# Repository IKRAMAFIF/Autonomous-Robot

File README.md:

# 🤖 Projet CATRONIC : Robot Autonome "Chat et Souris"

> **Auteurs :** AFIF Ikram, AIT ALLA Hajar, MENJLI Fakhri

> **Encadré par :** Laurent FIACK, Nicolas PAPAZOGLOU

> **Année académique :** 2025/2026

Le robot **CATRONIC** est un système embarqué autonome conçu pour simuler un jeu de chat et de souris entre plusieurs robots identiques. Les robots évoluent sur une table sans bordures et sont capables de détecter les bords pour éviter toute chute.

---

##  Table des matières
- [Stratégie de fonctionnement](#stratégie-de-fonctionnement)
- [Architecture du système](#architecture-du-système-global)
  - [Schémas généraux](#schémas-généraux)
  - [Sous-systèmes](#sous-systèmes)
- [Nomenclature (Bill of Materials)](#nomenclature-bill-of-materials)
- [Structure logicielle et FreeRTOS](#structure-logicielle-et-freertos)
- [Tests et validation](#tests-et-validation)
- [Test final](#test-final)
- [Conclusion](#conclusion)

---

##  Stratégie de fonctionnement

La logique du robot est orchestrée par un noyau temps réel (**FreeRTOS**), permettant de gérer plusieurs tâches simultanément pour une réactivité maximale.

### Détection de l'environnement

- **Détection des bords :** Le robot utilise des **capteurs mécaniques Würth WS-MITV** positionnés à l’avant, à l’arrière, à gauche et à droite. Lorsqu’un capteur détecte le vide, il déclenche une interruption qui ordonne un changement immédiat de direction pour éviter la chute.  
- **Détection des adversaires :** Le **LIDAR YDLIDAR X2** scanne l’environnement à 360° et transmet en temps réel la position et la distance des autres robots.  
- **Détection des collisions :** L’**accéléromètre ADXL343** détecte les chocs par variation brutale d’accélération. Il est également utilisé comme arrêt d’urgence manuel.

### Modes de jeu

- **Mode Souris 🐭 :** Le robot cherche à maximiser la distance avec le “chat” tout en évitant les bords de la table.  
- **Mode Chat 🐱 :** Le robot identifie la “souris” la plus proche via le LIDAR et cherche à la percuter.

---

##  Architecture du système global

L’architecture est organisée autour de cinq sous-ensembles principaux : **alimentation**, **commande**, **acquisition**, **déplacement** et **interface utilisateur**.

### Schémas généraux

Vues d’ensemble de l’architecture matérielle :

**Figure 1 – Diagramme d’architecture fonctionnelle du robot:**

**Figure 2 – Schéma global du système:**

**Figure 3 – Routage du PCB principal:**

**Figure 4 – Vue 3D du PCB sous KiCad:**

### Sous-systèmes

####  Alimentation
Le robot est alimenté par une batterie **NiMH 7.2V**, régulée en **5V** pour le LIDAR et en **3.3V** pour le reste des composants.

*Figure 5 – Schéma d’alimentation du robot.*

####  Commande
Le cœur du système repose sur un **STM32G431CBU6** (ARM Cortex-M4) exécutant **FreeRTOS** pour coordonner les différentes tâches.

*Figure 6 – Schéma de la carte de commande STM32.*

#### Acquisition
Ce sous-système regroupe les capteurs assurant la perception de l’environnement.

*Figure 7 – Sous-système de détection (LIDAR, accéléromètre, capteurs WS-MITV).* 

####  Déplacement
Deux moteurs DC, commandés par des **drivers ZXBM5210-SP-13**, permettent un contrôle précis de la vitesse et de la direction via des signaux PWM.

*Figure 8 – Schéma des moteurs et drivers.*

####  Interface utilisateur
Interrupteur, bouton de démarrage, LED de statut et connecteur SWD pour le débogage.

---

##  Nomenclature (Bill of Materials)

| Composant | Référence | Datasheet |
|:---|:---|:---|
| Microcontrôleur | STM32G431CBU6 | [Datasheet](https://www.st.com/resource/en/datasheet/stm32g431c6.pdf) |
| Driver moteur | ZXBM5210-SP-13 | [Datasheet](https://www.mouser.fr/datasheet/3/175/1/ZXBM5210.pdf) |
| Accéléromètre | ADXL343BCCZ-RL | [Datasheet](https://www.analog.com/media/en/technical-documentation/data-sheets/adxl343.pdf) |
| LIDAR | YDLIDAR X2 | [Datasheet](https://cdn.robotshop.com/media/y/ydl/rb-ydl-04/pdf/ydlidar-x2-360-laser-scanner-datasheet2.pdf) |
| Régulateur 5V | MP1475DJ-LF-P | [Datasheet](https://www.farnell.com/datasheets/2915024.pdf) |
| Régulateur 3.3V | BU33SD5WG-TR | [Datasheet](https://fscdn.rohm.com/en/products/databook/datasheet/ic/power/linear_regulator/buxxsd5wg-e.pdf) |
| Batterie | NiMH 7.2V 1.3Ah | [Datasheet](https://fr.rs-online.com/web/p/blocs-batteries-rechargeables/7770377) |
| Capteur bordure | WS-MITV THT | [Datasheet](https://www.we-online.com/en/components/products/MITV_12_8X5_8_THT__LEVER_LEFT_55GF) |
| Bluetooth | HC-05 | [Datasheet](https://components101.com/sites/default/files/component_datasheet/HC-05%20Datasheet.pdf) |
| Boutons poussoirs | Wurth 430182070816 | [Datasheet](https://www.we-online.com/components/products/datasheet/430182070816.pdf) |
| Interrupteur ON/OFF | Wurth 472121020311 | [Datasheet](https://www.we-online.com/components/products/datasheet/472121020311.pdf) |

---
## Fichiers sources principaux

-   **`main.c`** : Point d'entrée du programme. Ce fichier initialise le microcontrôleur, tous les périphériques (GPIO, I2C, UART, Timers), les pilotes (moteurs, LIDAR), et crée les quatre tâches FreeRTOS qui orchestrent le comportement du robot.
-   **`robot_logic.c`** : Cœur de l'intelligence du robot. Il contient l'implémentation des tâches FreeRTOS qui gèrent la logique de jeu, la détection des collisions et des bordures, ainsi que la communication.
-   **`MoteurPWM.c`** : Pilote pour le contrôle des moteurs DC. Il fournit des fonctions pour initialiser les moteurs, et contrôler leur vitesse via des signaux PWM.
-   **`ADXL343_driver.c`** : Pilote pour l'accéléromètre ADXL343. Il gère l'initialisation du capteur et la détection de chocs.
-   **`driver_LIDAR.c`** : Pilote pour le capteur LIDAR YDLIDAR X2. Il traite les données brutes reçues via UART DMA pour en extraire la distance et l'angle des obstacles.
-   **`border_sensors.c`** : Gère la logique des capteurs de bordure.
-   **`drv_bt.c`** : Assure la gestion de la communication Bluetooth (HC-05), notamment la réception de commandes.

##  Structure logicielle et FreeRTOS

Le comportement du robot est géré par **quatre tâches FreeRTOS** principales :

1.  **`BorderTask`**
    -   **Rôle :** Surveille en permanence les capteurs de bordure.
    -   **Fonctionnement :** À intervalle régulier (100 ms), la tâche lit l'état des capteurs. Si un bord est détecté, elle met à jour une variable globale (`border_active`) protégée par un mutex pour signaler l'état et la direction du bord détecté à la tâche principale `RobotModeTask`.

2.  **`ShockTask`**
    -   **Rôle :** Détecte les collisions et inverse les rôles "Chat" et "Souris".
    -   **Fonctionnement :** La tâche initialise l'accéléromètre pour la détection de chocs. Elle vérifie en continu si un choc a eu lieu. Si c'est le cas, elle change l'état du robot (`robot_mode`) de `CHAT` à `SOURIS` ou inversement.

3.  **`BluetoothTask`**
    -   **Rôle :** Traite les commandes reçues via Bluetooth.
    -   **Fonctionnement :** La tâche attend de recevoir des commandes utilisateur. Elle peut ainsi forcer le robot à s'arrêter (`STOP`), à démarrer (`START`), ou à passer en mode `CHAT` ou `SOURIS`, offrant un contrôle manuel sur le comportement du robot.

4.  **`RobotModeTask`**
    -   **Rôle :** Tâche principale qui exécute la logique de déplacement et de jeu.
    -   **Fonctionnement :** C'est la tâche la plus complexe. À chaque cycle :
        -   Elle vérifie l'état de la variable `border_active`. Si un bord est détecté, elle exécute une manœuvre d'évitement prioritaire (reculer puis tourner) pour empêcher le robot de tomber.
        -   Si aucun bord n'est détecté, elle exécute la logique de jeu en fonction de la variable `robot_mode` :
            -   **Mode `ROBOT_STOP` :** Les moteurs sont à l'arrêt.
            -   **Mode `ROBOT_MODE_CHAT` (Poursuite) :** La tâche analyse les données du LIDAR pour trouver l'obstacle le plus proche. Si l'obstacle est en face, elle commande au robot d'avancer. Sinon, elle le fait tourner pour se diriger vers la cible.
            -   **Mode `ROBOT_MODE_SOURIS` (Fuite) :** Si un obstacle (le "chat") est détecté à moins de 30 cm, le robot recule pour s'en éloigner. Sinon, il continue d'avancer pour explorer la zone de jeu.
        -   Si aucun obstacle n'est détecté par le LIDAR, le robot s'arrête.

---

##  Tests et validation

Pour garantir la fiabilité du système, plusieurs séries de tests ont été menées.

### Test de déplacement et moteurs

Ce test valide le contrôle PWM et met en évidence les écarts de vitesse entre les moteurs. 
Un ajustement asymétrique des vitesses a permis d’améliorer la précision du déplacement du robot.

### Test de détection de bordures/détection de collision

Ce test est crucial pour la sécurité du robot. Il valide la robustesse des capteurs mécaniques, et la détection des chocs via l'accéléromètre qui déclenche le changement de rôle du robot
- **Approche frontale :** Le robot est dirigé droit vers le bord de la table. On vérifie qu'il s'arrête et recule à chaque fois, sans chute.
- **Approche en diagonale :** Le test est répété avec différents angles d'approche pour s'assurer que le levier du capteur est bien actionné même lorsque le robot n'est pas perpendiculaire au bord.
- **Fiabilité :** Répétition du test des dizaines de fois pour garantir la reproductibilité et la fiabilité du mécanisme.
- **Changement de mode après impact :** Après une collision détectée par l'accéléromètre, on vérifie que les rôles "Chat" et "Souris" sont bien inversés.

*Figure 9 – Détection de bordures/chocs et changement de direction.*

### Test du LIDAR et logique de jeu

Ce test valide la perception de l'environnement et la stratégie comportementale.
- **Fiabilité de la détection d'adversaire :** Vérification que le LIDAR détecte de manière fiable la position de l'autre robot.
- **Logique de poursuite/fuite :** Validation de la trajectoire du robot en fonction des données du LIDAR (le "Chat" se rapproche de la "Souris", et la "Souris" s'en éloigne).

*Figure 10 – Données LIDAR capturées via Tera Term (UART DMA).* 

### Test Bluetooth

Ce test vérifie la connectivité et la fiabilité de la communication sans fil via le module Bluetooth HC-05.

- **Connexion :** Vérification de l'établissement de la connexion Bluetooth avec un appareil externe.

- **Transmission de données :** Test de l'envoi et de la réception de données entre le robot et l'appareil connecté.

- **Changement de mode à distance :** Validation de la capacité à modifier le rôle du robot (Chat/Souris) via une commande Bluetooth.

*Figure 11 – Communication Bluetooth et affichage des données.*

---
## Structure du dépôt GitHub

```
├── Firmware/           → Code STM32CubeIDE 
├── Hardware/           → Schémas, PCB et vues 3D KiCad
├── Media/              → Illustrations et résultats de tests
└── README.md           → Présentation du projet
```

---
##  Test final

Lors du test final, le robot a validé plusieurs fonctionnalités clés. Les capteurs de bordure fonctionnent correctement, permettant au robot de détecter les limites de la surface et d’éviter toute chute. La commande via Bluetooth est également opérationnelle : il est possible de sélectionner le mode de fonctionnement du robot ainsi que d’envoyer des commandes Start et Stop pour lancer ou arrêter le système. Les données du LiDAR ont pu être lues avec succès, cependant toutes les mesures n’étaient pas fiables et l’intégration complète du capteur dans le système embarqué n’a pas pu être finalisée. En conséquence, le robot n’est pas capable de détecter les autres robots à ce stade. Enfin, l’accéléromètre permet de détecter les chocs lors d’une collision, déclenchant automatiquement un changement de mode de fonctionnement du robot.

---
## Conclusion

Ce projet a permis de concevoir et de mettre en œuvre un robot mobile intégrant plusieurs capteurs et modes de fonctionnement. Les tests finaux ont validé avec succès la détection des bordures, la commande via Bluetooth avec sélection des modes ainsi que la gestion des collisions à l’aide de l’accéléromètre. Ces fonctionnalités assurent un fonctionnement sûr et contrôlable du robot.

Cependant, certains défis techniques ont été rencontrés, notamment lors de l’exploitation et de l’intégration du LiDAR. Bien que les données aient pu être lues, leur fiabilité et leur intégration complète dans l’architecture embarquée n’ont pas pu être finalisées, empêchant la détection des autres robots. Ces limitations sont principalement liées aux contraintes de temps et à la complexité du traitement des données capteur.

Ce travail a néanmoins permis d’acquérir une expérience pratique solide en systèmes embarqués, en communication sans fil et en intégration capteurs. Des perspectives d’amélioration incluent l’optimisation du traitement des données LiDAR, l’amélioration de la fusion capteurs et l’extension des capacités de détection du robot.

---

<p align="center">
  2026 — Projet académique ENSEA
  <br>Développement d’un robot autonome Chat–Souris 
</p>

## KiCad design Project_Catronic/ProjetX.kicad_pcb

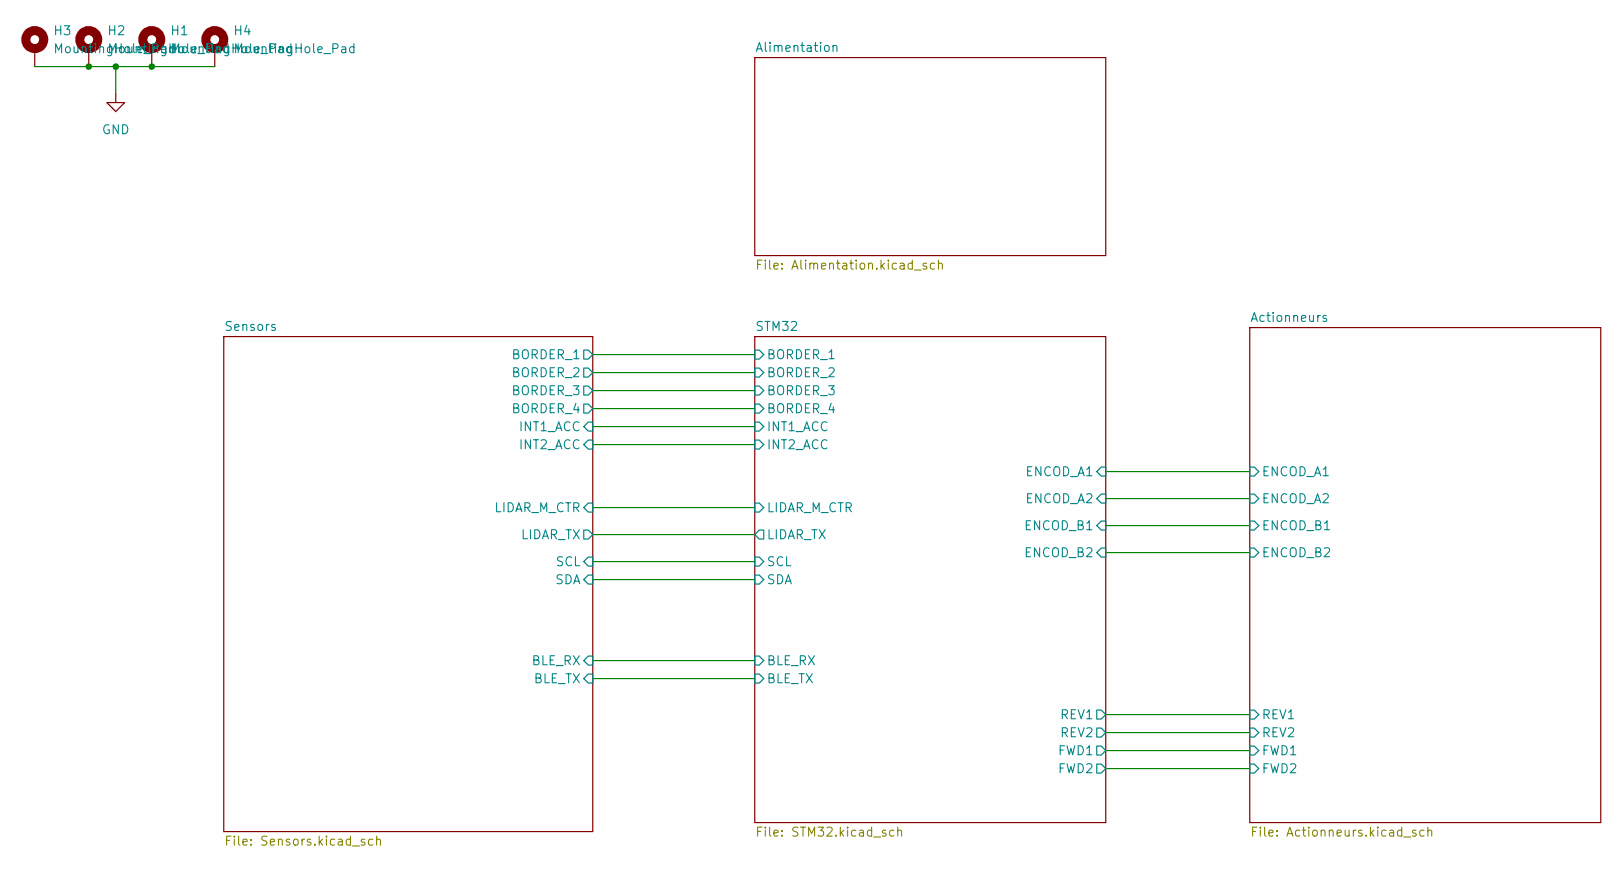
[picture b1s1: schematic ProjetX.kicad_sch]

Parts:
H1, H2, H3, H4: MountingHole_Pad; MountingHole_3.2mm_M3_Pad_Via

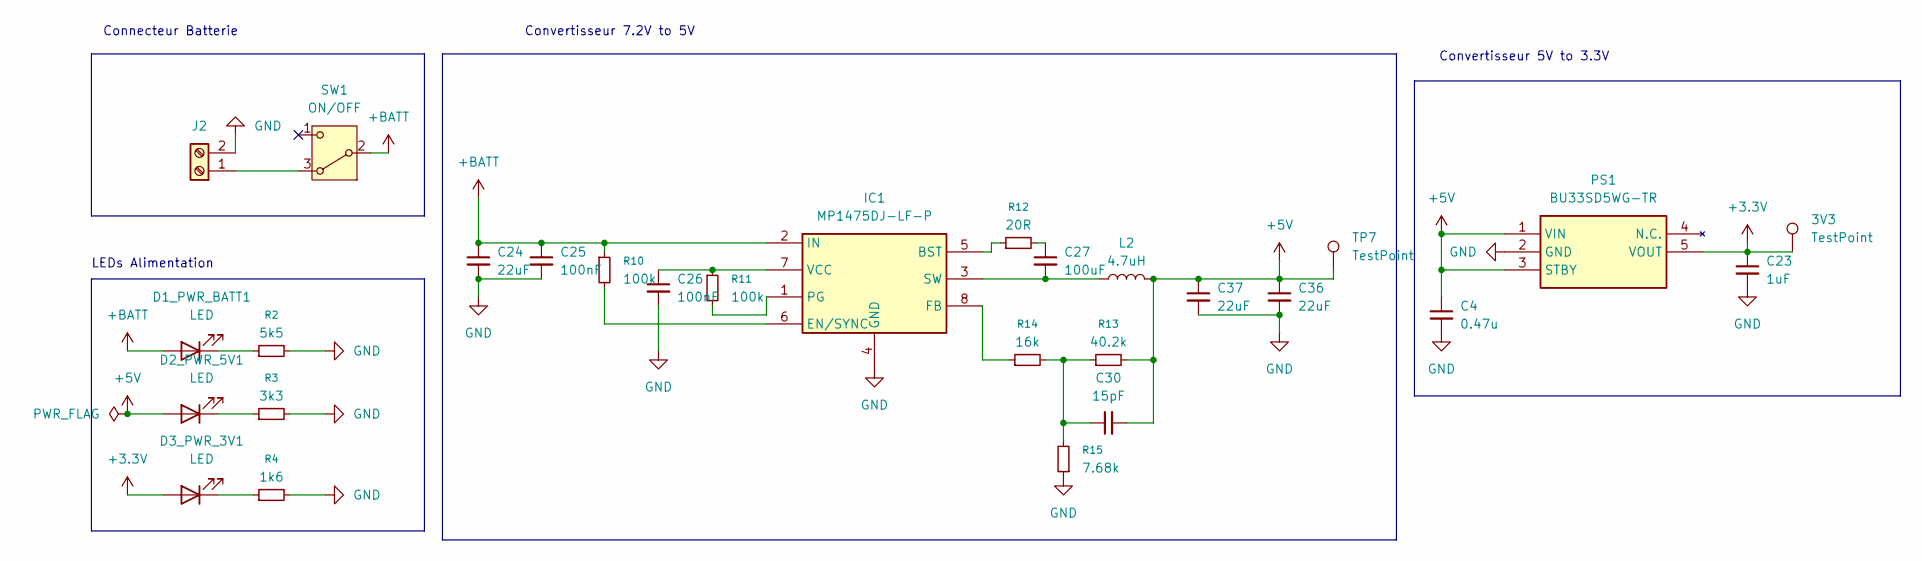
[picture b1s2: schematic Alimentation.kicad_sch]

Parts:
3V3: TestPoint; TestPoint_Pad_D1.0mm
C4: 0.47u; C_0402_1005Metric
C23: 1uF; C_0402_1005Metric
C24, C36, C37: 22uF; C_0805_2012Metric
C25, C26: 100nF; C_0402_1005Metric
C27: 100uF; C_0402_1005Metric
C30: 15pF; C_0402_1005Metric
D1_PWR_BATT1: LED; LED_0603_1608Metric; MPN 150060GS55040
D2_PWR_5V1: LED; LED_0603_1608Metric; MPN 150060BS55040
D3_PWR_3V1: LED; LED_0603_1608Metric; MPN 150060RS55040
IC1: MP1475DJ-LF-P; TSOT-23-8; Manufacturer_Part_Number MP1475DJ-LF-P
J2: Screw_Terminal_01x02; JST_XH_S2B-XH-A_1x02_P2.50mm_Horizontal
L2: 4.7uH; L_Wuerth_HCI-5040
PS1: BU33SD5WG-TR; TSOT-23-5; Manufacturer_Part_Number BU33SD5WG-TR
R2: 5k5; R_0402_1005Metric
R3: 3k3; R_0402_1005Metric
R4: 1k6; R_0402_1005Metric
R10, R11: 100k; R_0402_1005Metric
R12: 20R; R_0402_1005Metric
R13: 40.2k; R_0402_1005Metric
R14: 16k; R_0402_1005Metric
R15: 7.68k; R_0402_1005Metric
SW1: ON/OFF; Nidec_Copal_CAS-120A; MPN 777-0377
TP7: TestPoint; TestPoint_Pad_D1.0mm

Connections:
+3.3V: 3V3.1, C23.1, D3_PWR_3V1.2 (A), PS1.5 (VOUT); also elsewhere on the board
+5V: C4.1, C30.2, C36.1, C37.1, D2_PWR_5V1.2 (A), L2.2, PS1.1 (VIN), PS1.3 (STBY), R13.2, TP7.1; also elsewhere on the board
+BATT: C24.1, C25.1, D1_PWR_BATT1.2 (A), IC1.2 (IN), R10.1, SW1.2 (B); also elsewhere on the board
unnamed: C27.1, R12.2
unnamed: C30.1, R13.1, R14.2, R15.2
unnamed: D1_PWR_BATT1.1 (K), R2.1
unnamed: D2_PWR_5V1.1 (K), R3.1
unnamed: D3_PWR_3V1.1 (K), R4.1
unnamed: IC1.5 (BST), R12.1
unnamed: IC1.6 (EN/SYNC), R10.2
unnamed: IC1.8 (FB), R14.1
unnamed: IC1.1 (PG), R11.2
unnamed: C27.2, IC1.3 (SW), L2.1
unnamed: C26.1, IC1.7 (VCC), R11.1

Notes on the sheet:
Convertisseur 7.2V to 5V
Connecteur Batterie
Convertisseur 5V to 3.3V
LEDs Alimentation

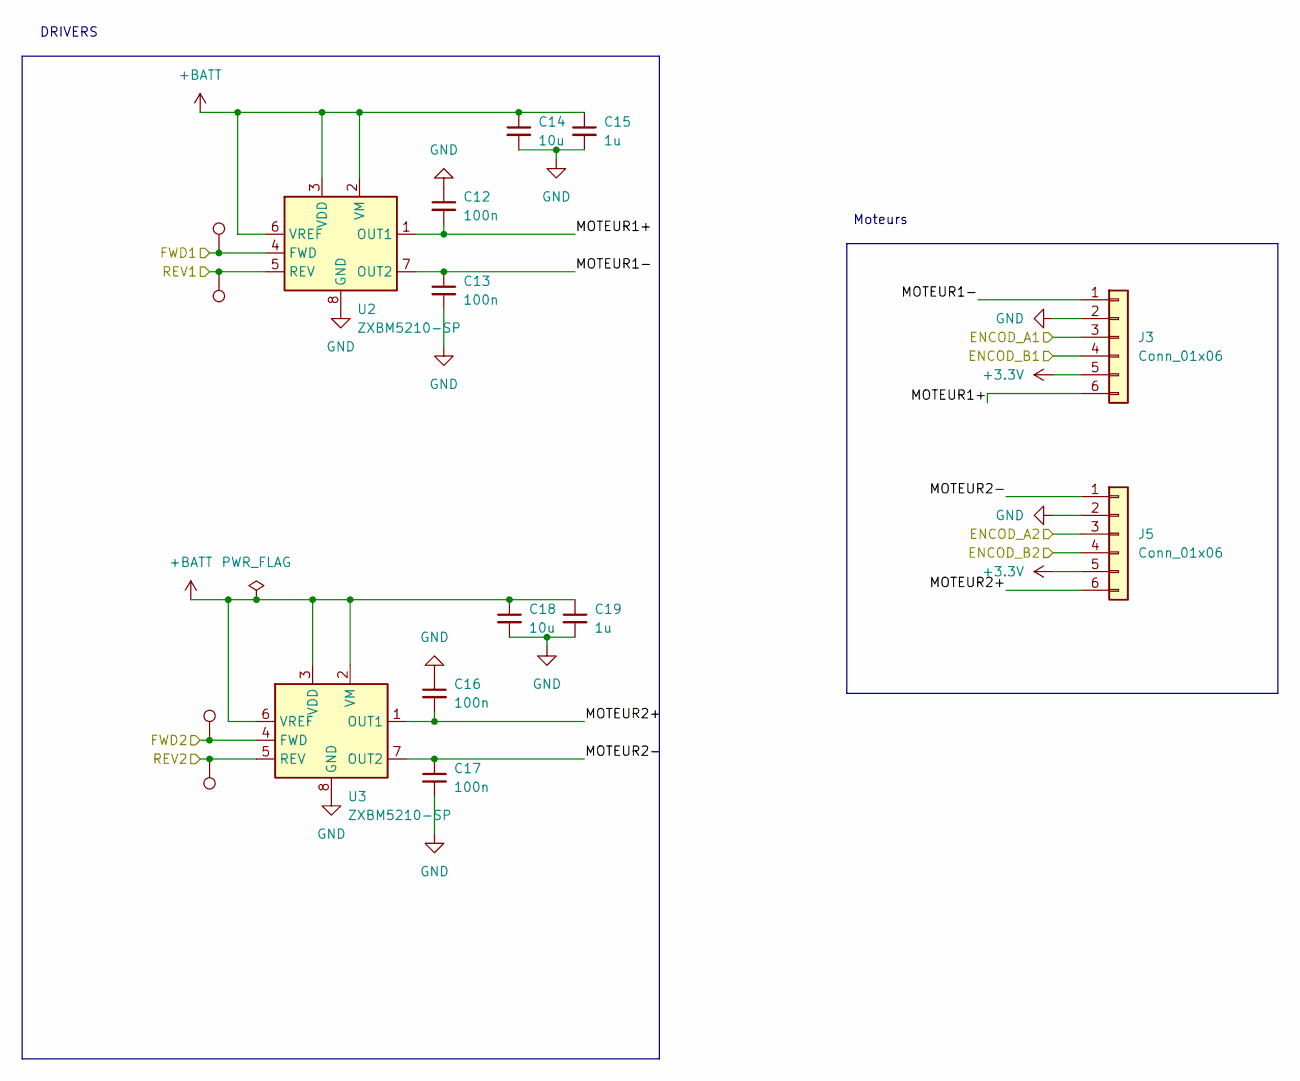
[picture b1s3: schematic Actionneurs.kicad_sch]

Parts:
C12, C13, C16, C17: 100n; C_0402_1005Metric
C14, C18: 10u; C_0402_1005Metric
C15, C19: 1u; C_0402_1005Metric
J3, J5: Conn_01x06; JST_XH_S6B-XH-A_1x06_P2.50mm_Horizontal; MPN DfRobot FIT0521
TP1, TP2, TP3, TP4: TestPoint; TestPoint_Pad_D1.0mm
U2, U3: ZXBM5210-SP; Diodes_SO-8EP; MPN ZXBM5210-SP

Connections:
+3.3V: J3.5, J5.5; also elsewhere on the board
+BATT: C14.1, C15.1, C18.1, C19.1, U2.2 (VM), U2.3 (VDD), U2.6 (VREF), U3.2 (VM), U3.3 (VDD), U3.6 (VREF); also elsewhere on the board
/Actionneurs/ENCOD_A1: J3.3; also elsewhere on the board
/Actionneurs/ENCOD_A2: J5.3; also elsewhere on the board
/Actionneurs/ENCOD_B1: J3.4; also elsewhere on the board
/Actionneurs/ENCOD_B2: J5.4; also elsewhere on the board
/Actionneurs/FWD1: TP1.1, U2.4 (FWD); also elsewhere on the board
/Actionneurs/FWD2: TP3.1, U3.4 (FWD); also elsewhere on the board
/Actionneurs/MOTEUR1+: C12.2, J3.6, U2.1 (OUT1)
/Actionneurs/MOTEUR1-: C13.1, J3.1, U2.7 (OUT2)
/Actionneurs/MOTEUR2+: C16.2, J5.6, U3.1 (OUT1)
/Actionneurs/MOTEUR2-: C17.1, J5.1, U3.7 (OUT2)
/Actionneurs/REV1: TP2.1, U2.5 (REV); also elsewhere on the board
/Actionneurs/REV2: TP4.1, U3.5 (REV); also elsewhere on the board

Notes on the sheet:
DRIVERS
Moteurs

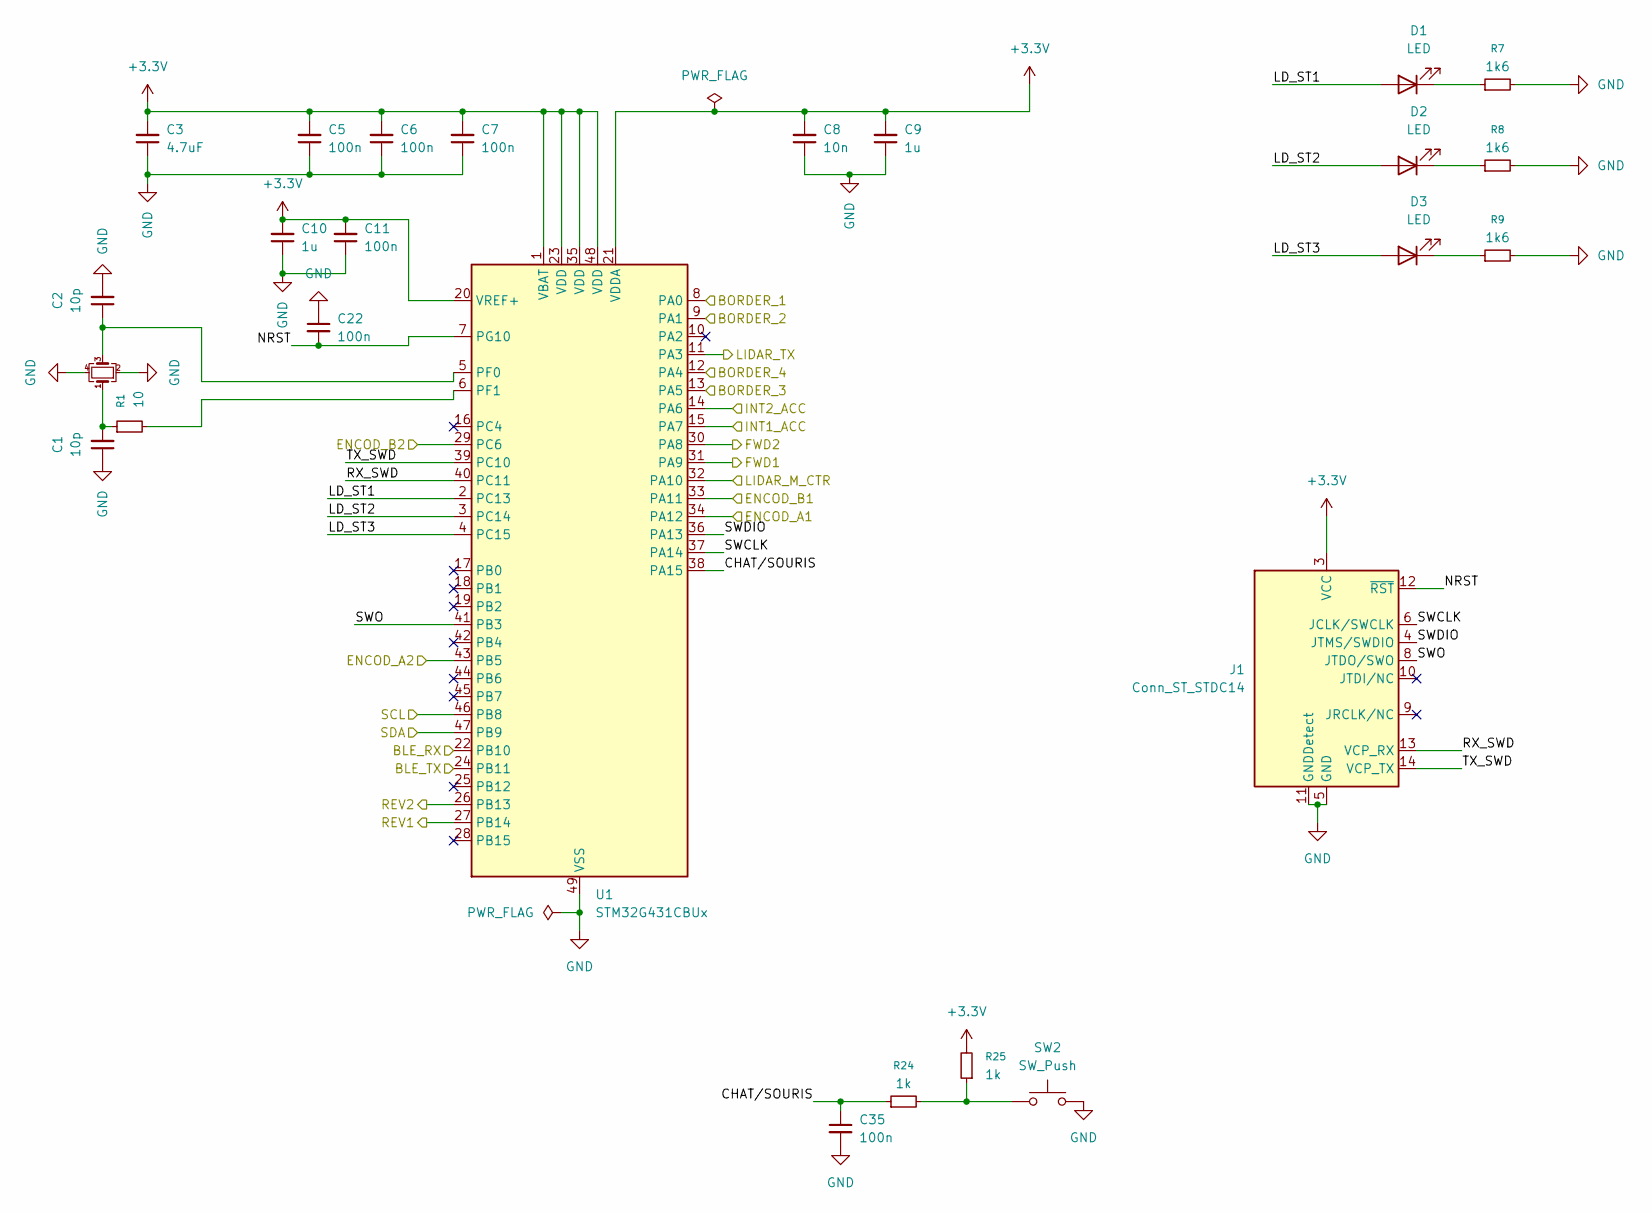
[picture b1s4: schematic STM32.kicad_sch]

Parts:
C1, C2: 10p; C_0402_1005Metric
C3: 4.7uF; C_0603_1608Metric
C5, C6, C7, C11, C22, C35: 100n; C_0402_1005Metric
C8: 10n; C_0402_1005Metric
C9, C10: 1u; C_0402_1005Metric
D1, D2, D3: LED; LED_0603_1608Metric; MPN 150060RS55040
J1: Conn_ST_STDC14; PinHeader_2x07_P1.27mm_Vertical_SMD; MPN SAMTEC FTSH-107-01-L-DV-K-A.
R1: 10; R_0402_1005Metric
R7, R8, R9: 1k6; R_0402_1005Metric
R24, R25: 1k; R_0402_1005Metric
SW2: SW_Push; SW_PUSH_6mm_H9.5mm
U1: STM32G431CBUx; QFN-48-1EP_7x7mm_P0.5mm_EP5.6x5.6mm; MPN STM32G4316B
Y1: Crystal_GND24_Small; Crystal_SMD_EuroQuartz_MT-4Pin_3.2x2.5mm

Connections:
+3.3V: C3.2, C5.2, C6.2, C7.2, C8.2, C9.2, C10.2, C11.2, J1.3 (VCC), R25.2, U1.1 (VBAT), U1.20 (VREF+), U1.21 (VDDA), U1.23 (VDD), U1.35 (VDD), U1.48 (VDD); also elsewhere on the board
/Actionneurs/ENCOD_A1: U1.34 (PA12); also elsewhere on the board
/Actionneurs/ENCOD_A2: U1.43 (PB5); also elsewhere on the board
/Actionneurs/ENCOD_B1: U1.33 (PA11); also elsewhere on the board
/Actionneurs/ENCOD_B2: U1.29 (PC6); also elsewhere on the board
/Actionneurs/FWD1: U1.31 (PA9); also elsewhere on the board
/Actionneurs/FWD2: U1.30 (PA8); also elsewhere on the board
/Actionneurs/REV1: U1.27 (PB14); also elsewhere on the board
/Actionneurs/REV2: U1.26 (PB13); also elsewhere on the board
/STM32/BLE_RX: U1.22 (PB10); also elsewhere on the board
/STM32/BLE_TX: U1.24 (PB11); also elsewhere on the board
/STM32/BORDER_1: U1.8 (PA0); also elsewhere on the board
/STM32/BORDER_2: U1.9 (PA1); also elsewhere on the board
/STM32/BORDER_3: U1.13 (PA5); also elsewhere on the board
/STM32/BORDER_4: U1.12 (PA4); also elsewhere on the board
/STM32/CHAT/SOURIS: C35.1, R24.1, U1.38 (PA15)
/STM32/INT1_ACC: U1.15 (PA7); also elsewhere on the board
/STM32/INT2_ACC: U1.14 (PA6); also elsewhere on the board
/STM32/LD_ST1: D1.2 (A), U1.2 (PC13)
/STM32/LD_ST2: D2.2 (A), U1.3 (PC14)
/STM32/LD_ST3: D3.2 (A), U1.4 (PC15)
/STM32/LIDAR_M_CTR: U1.32 (PA10); also elsewhere on the board
/STM32/LIDAR_TX: U1.11 (PA3); also elsewhere on the board
/STM32/NRST: C22.2, J1.12 (~RST), U1.7 (PG10)
/STM32/RX_SWD: J1.13 (VCP_RX), U1.40 (PC11)
/STM32/SCL: U1.46 (PB8); also elsewhere on the board
/STM32/SDA: U1.47 (PB9); also elsewhere on the board
/STM32/SWCLK: J1.6 (JCLK/SWCLK), U1.37 (PA14)
/STM32/SWDIO: J1.4 (JTMS/SWDIO), U1.36 (PA13)
/STM32/SWO: J1.8 (JTDO/SWO), U1.41 (PB3)
/STM32/TX_SWD: J1.14 (VCP_TX), U1.39 (PC10)
unnamed: C1.2, R1.1, Y1.1
unnamed: D1.1 (K), R7.1
unnamed: D2.1 (K), R8.1
unnamed: D3.1 (K), R9.1
unnamed: R24.2, R25.1, SW2.1
unnamed: C2.1, U1.5 (PF0), Y1.3
unnamed: R1.2, U1.6 (PF1)

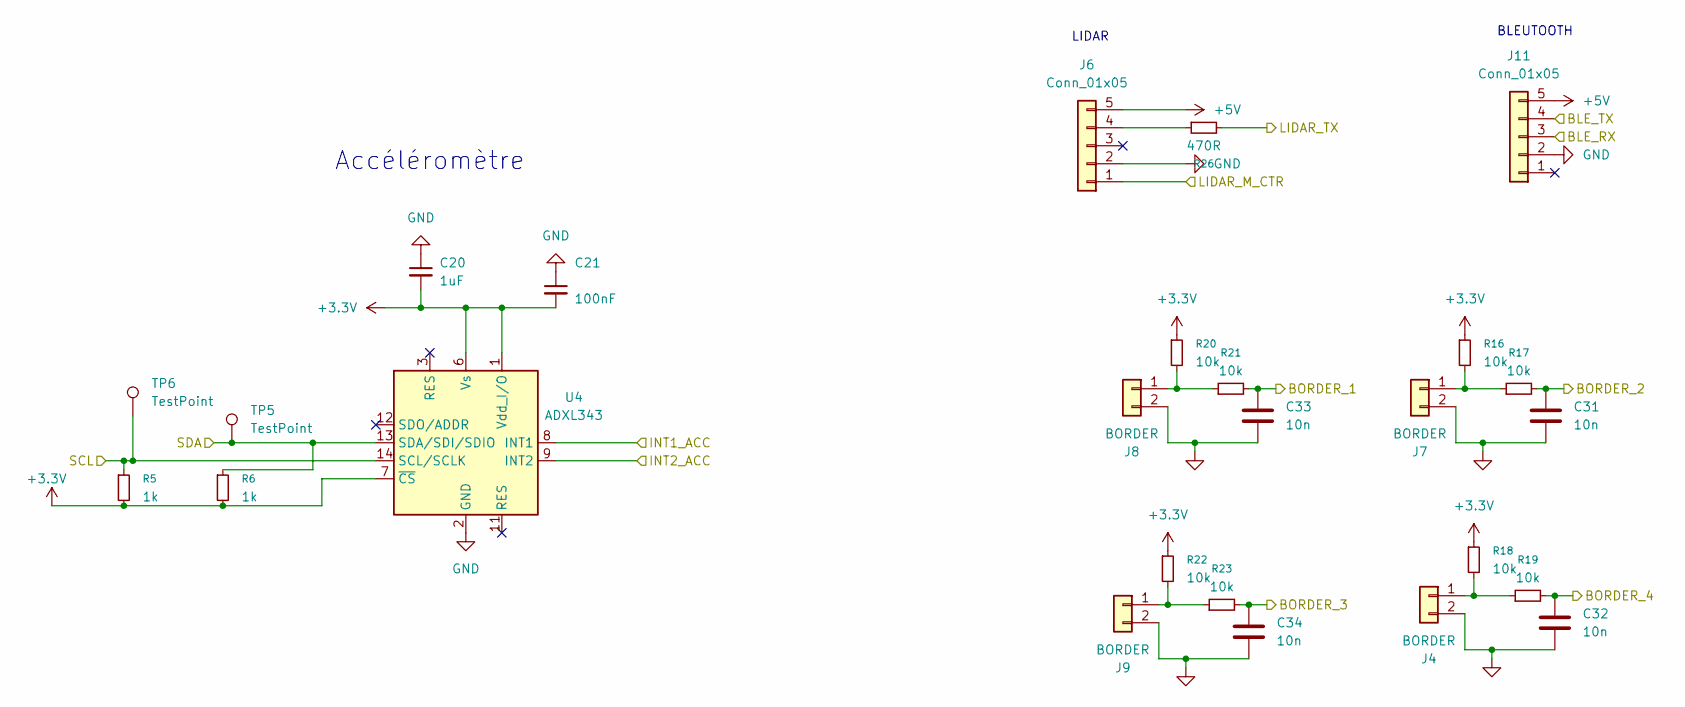
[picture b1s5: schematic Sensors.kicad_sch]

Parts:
C20: 1uF; C_0402_1005Metric
C21: 100nF; C_0402_1005Metric
C31, C32, C33, C34: 10n; C_0402_1005Metric
J4, J7, J8, J9: BORDER; JST_XH_S2B-XH-A_1x02_P2.50mm_Horizontal
J6: Conn_01x05; JST_XH_S5B-XH-A_1x05_P2.50mm_Horizontal; MPN YDLIDAR X2
J11: Conn_01x05; JST_XH_S5B-XH-A_1x05_P2.50mm_Horizontal
R5, R6: 1k; R_0402_1005Metric
R16, R17, R18, R19, R20, R21, R22, R23: 10k; R_0402_1005Metric
R26: 470R; R_0402_1005Metric
TP5, TP6: TestPoint; TestPoint_Pad_D1.0mm
U4: ADXL343; LGA-14_3x5mm_P0.8mm_LayoutBorder1x6y; MPN ADXL343BCCZ-RL

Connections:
+3.3V: C20.2, C21.2, R5.2, R6.2, R16.1, R18.1, R20.1, R22.1, U4.1 (Vdd_I/O), U4.6 (Vs), U4.7 (~CS); also elsewhere on the board
+5V: J6.5, J11.5; also elsewhere on the board
/STM32/BLE_RX: J11.3; also elsewhere on the board
/STM32/BLE_TX: J11.4; also elsewhere on the board
/STM32/BORDER_1: C33.1, R21.2; also elsewhere on the board
/STM32/BORDER_2: C31.1, R17.2; also elsewhere on the board
/STM32/BORDER_3: C34.1, R23.2; also elsewhere on the board
/STM32/BORDER_4: C32.1, R19.2; also elsewhere on the board
/STM32/INT1_ACC: U4.8 (INT1); also elsewhere on the board
/STM32/INT2_ACC: U4.9 (INT2); also elsewhere on the board
/STM32/LIDAR_M_CTR: J6.1; also elsewhere on the board
/STM32/LIDAR_TX: R26.2; also elsewhere on the board
/STM32/SCL: R5.1, TP6.1, U4.14 (SCL/SCLK); also elsewhere on the board
/STM32/SDA: R6.1, TP5.1, U4.13 (SDA/SDI/SDIO); also elsewhere on the board
unnamed: J4.1, R18.2, R19.1
unnamed: J6.4, R26.1
unnamed: J7.1, R16.2, R17.1
unnamed: J8.1, R20.2, R21.1
unnamed: J9.1, R22.2, R23.1

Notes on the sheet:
Accéléromètre
BLEUTOOTH
LIDAR

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
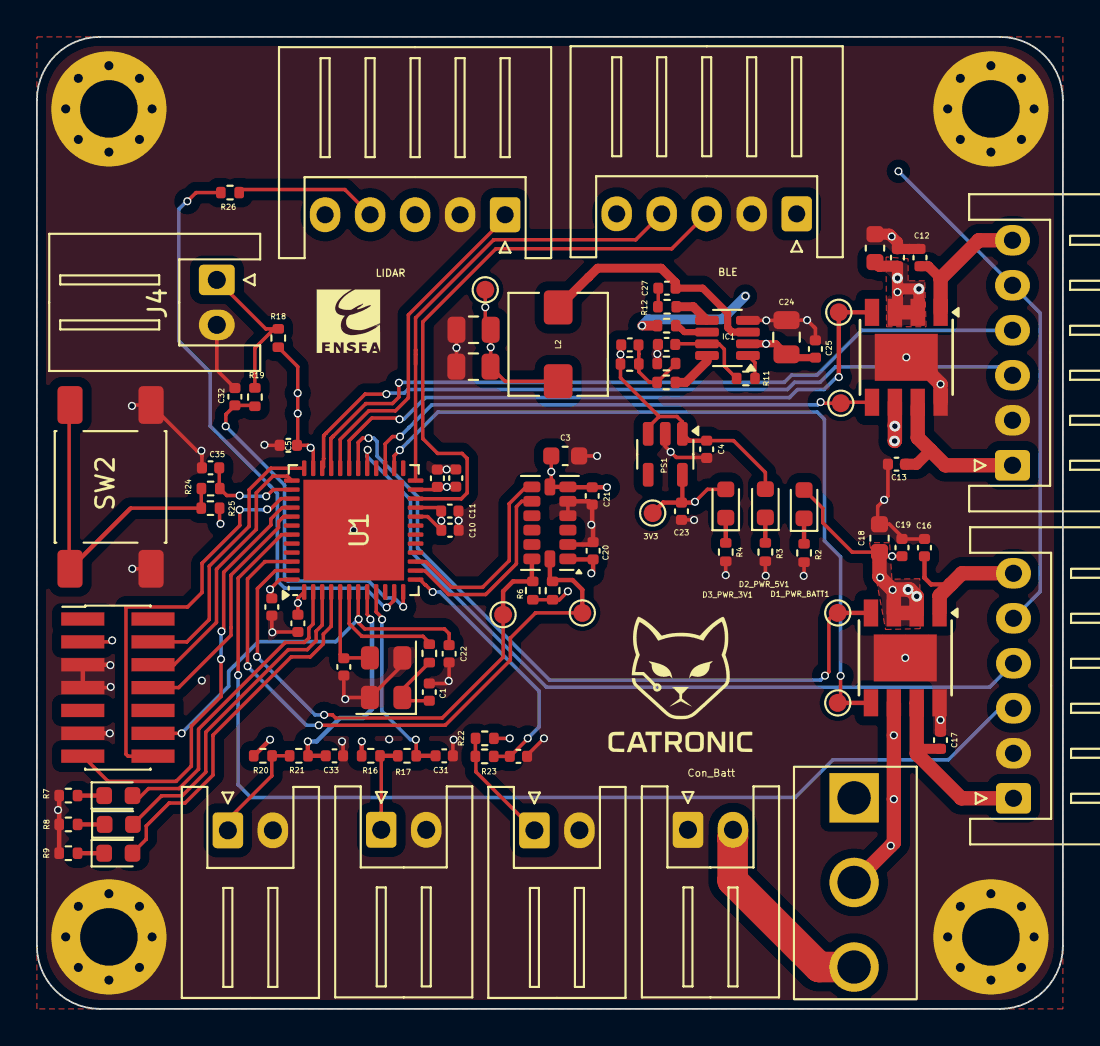
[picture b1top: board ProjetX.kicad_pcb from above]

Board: 4 copper layers, 57.0 x 54.0 mm, 99 parts (0 on the bottom side), 62 nets.

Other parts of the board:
S1: 1101M2S3CQE2; sw wurth

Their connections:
+BATT: S1.2; also elsewhere on the board

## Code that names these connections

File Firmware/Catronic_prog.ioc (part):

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Mcu.Name=STM32G431C(6-8-B)Ux
Mcu.Package=UFQFPN48
Mcu.UserName=STM32G431CBUx
PA0.GPIOParameters=GPIO_Label
PA0.GPIO_Label=BORDER_1
PA0.Signal=GPIO_Input
PA1.GPIOParameters=GPIO_Label
PA1.GPIO_Label=BORDER_2
PA1.Signal=GPIO_Input
PA10.Signal=GPIO_Output
PA11.GPIOParameters=GPIO_Label
PA11.GPIO_Label=ENCOD_B1
PA11.Signal=S_TIM4_CH1
PA12.GPIOParameters=GPIO_Label
PA12.GPIO_Label=ENCOD_A1
PA12.Signal=S_TIM4_CH2
PA13.GPIOParameters=GPIO_Label
PA13.GPIO_Label=SWDIO
PA13.Mode=Trace_Asynchronous_SW
PA13.Signal=SYS_JTMS-SWDIO
PA14.GPIOParameters=GPIO_Label
PA14.GPIO_Label=SWCLK
PA14.Mode=Trace_Asynchronous_SW
PA14.Signal=SYS_JTCK-SWCLK
PA15.Signal=GPIO_Output
PA2.GPIOParameters=GPIO_Label
PA2.GPIO_Label=LIDAR_TX
PA2.Mode=Asynchronous
PA2.Signal=USART2_TX
PA3.GPIOParameters=GPIO_Label
PA3.GPIO_Label=LIDAR_RX
PA3.Mode=Asynchronous
PA3.Signal=USART2_RX
PA4.GPIOParameters=GPIO_Label
PA4.GPIO_Label=BORDER_4
PA4.Signal=GPIO_Input
PA5.GPIOParameters=GPIO_PuPd,GPIO_Label
PA5.GPIO_Label=BORDER_3
PA5.GPIO_PuPd=GPIO_NOPULL
PA5.Signal=GPIO_Input
PA6.GPIOParameters=GPIO_Label
PA6.GPIO_Label=INT2_ACC
PA6.Signal=GPIO_Input
PA7.GPIOParameters=GPIO_Label
PA7.GPIO_Label=INT1_ACC
PA7.Signal=GPIO_Input
PA8.GPIOParameters=GPIO_Label
PA8.GPIO_Label=FWD2
PA8.Signal=S_TIM1_CH1
PA9.GPIOParameters=GPIO_Label
PA9.GPIO_Label=FWD1
PA9.Signal=S_TIM1_CH2
PB10.GPIOParameters=GPIO_Label
PB10.GPIO_Label=BLE_TX
PB10.Mode=Asynchronous
PB10.Signal=USART3_TX
PB11.GPIOParameters=GPIO_Label
PB11.GPIO_Label=BLE_RX
PB11.Mode=Asynchronous
PB11.Signal=USART3_RX
PB13.GPIOParameters=GPIO_Label
PB13.GPIO_Label=REV2
PB13.Mode=PWM Generation1 CH1 CH1N
PB13.Signal=TIM1_CH1N
PB14.GPIOParameters=GPIO_Label
PB14.GPIO_Label=REV1
PB14.Mode=PWM Generation2 CH2 CH2N
PB14.Signal=TIM1_CH2N
PB3.GPIOParameters=GPIO_Label
PB3.GPIO_Label=SWO
PB3.Mode=Trace_Asynchronous_SW
PB3.Signal=SYS_JTDO-SWO
PB5.GPIOParameters=GPIO_Label
PB5.GPIO_Label=ENCOD_A2
PB5.Signal=S_TIM3_CH2
PB7.Mode=Asynchronous
PB7.Signal=USART1_RX
PB8-BOOT0.GPIOParameters=GPIO_Label
PB8-BOOT0.GPIO_Label=SCL
PB8-BOOT0.Mode=I2C
PB8-BOOT0.Signal=I2C1_SCL
PB9.GPIOParameters=GPIO_Label
PB9.GPIO_Label=SDA
PB9.Mode=I2C
PB9.Signal=I2C1_SDA
PC10.GPIOParameters=GPIO_Label
PC10.GPIO_Label=SWD_TX
PC10.Mode=Asynchronous
PC10.Signal=UART4_TX
PC11.GPIOParameters=GPIO_Label
PC11.GPIO_Label=SWD_RX
PC11.Mode=Asynchronous
PC11.Signal=UART4_RX
PC13.GPIOParameters=GPIO_Label
PC13.GPIO_Label=LED_ST1
PC13.Signal=GPIO_Output
PC14-OSC32_IN.GPIOParameters=GPIO_Label
PC14-OSC32_IN.GPIO_Label=LED_ST2
PC14-OSC32_IN.Signal=GPIO_Output
PC15-OSC32_OUT.GPIOParameters=GPIO_Label
PC15-OSC32_OUT.GPIO_Label=LED_ST3
PC15-OSC32_OUT.Signal=GPIO_Output
PC4.Mode=Asynchronous
PC4.Signal=USART1_TX
PC6.GPIOParameters=GPIO_Label
PC6.GPIO_Label=ENCOD_B2
PC6.Signal=S_TIM3_CH1
RCC.HSE_VALUE=8000000
RCC.SYSCLKFreq_VALUE=170000000
RCC.SYSCLKSource=RCC_SYSCLKSOURCE_PLLCLK
board=custom

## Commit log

2025-09-22 first commit from this laptop.
2025-09-24 Update KiCad schematics
2025-09-24 Updated project
2025-09-24 Clean repo: ignore KiCad backup/autosave files
2025-10-01 Replaced old project folder with ProjetX
2025-10-01 Renamed folder to Projet_Robot_Autonome
2025-10-06 Updated KiCad project files
2025-10-13 Clean repository before re-upload
2025-10-13 Rename project folder to Project_Catronic
2025-10-13 Update KiCad project with latest schematic and PCB edits
2025-10-13 Update KiCad project files (Project_Catronic)
2025-11-25 Rename ProjetX.kicad_sch to ProjetCatronic.kicad_sch
2025-11-25 Rename ProjetX.kicad_pcb to ProjetCatronic.kicad_pcb
2025-11-25 Rename ProjetX.kicad_prl to ProjetCatronic.kicad_prl
2025-11-25 Rename ProjetX.kicad_pro to ProjetCatronic.kicad_pro
2025-11-25 Rename ~ProjetX.kicad_pcb.lck to ~ProjetCatronic.kicad_pcb.lck
2025-11-25 Rename ~ProjetX.kicad_sch.lck to ~ProjetCatronic.kicad_sch.lck
2025-12-02 sofware
2025-12-02 Enhance README with system architecture and power info
    Added system architecture and power regulation details to README.
2025-12-02 Driver Moteur
2025-12-02 Create pic
2025-12-03 Driver lidar +bleutooth
2026-01-09 Refine project description for CATRONIC
    Clarified the project description and removed redundancy.
2026-01-14 Update architecture diagram image format to PNG
2026-01-14 Revise README for project overview and organization
    Updated the README to enhance project description and structure.
2026-01-14 Revise authors and enhance README with images
    Updated author names and added images with captions in the README.
2026-01-15 tache freeRTOS
2026-01-15 avancement sur la tache de lidar
2026-01-15 mise a jour
2026-01-16 Enhance README with new tests and visualizations
    Added new tests for Bluetooth communication and LIDAR functionality, including visualizations and descriptions. Updated existing sections with images and clarified test descriptions.
2026-01-16 Update README with new images and collision test section
    Added additional images and a new section for collision detection testing.
2026-01-16 Remove challenges and improvement suggestions from README
    Removed sections on challenges faced and improvement suggestions in the project conclusion.
2026-01-16 Enhance README with project structure and software details
    Updated the edge detection section to specify the number of edge sensors and added a project structure section along with software architecture details, including diagrams and main source files.
2026-01-16 Enhance README with emojis and formatting updates
2026-01-16 Fix formatting in README.md sections
2026-01-16 Rename Project_Catronic/logo1.jpg to Project_Catronic/Images/logo1.jpg
2026-01-16 Rename Project_Catronic/logo2.jpg to Project_Catronic/Image/logo2.jpg
2026-01-16 Rename logo2.jpg to logo2.jpg
2026-01-16 organisation
2026-01-16 Fix image paths in README.md
    Updated image paths in README.md to reflect new directory structure.
2026-01-16 Refine communication interface description in README
2026-01-16 Add final test section and update conclusion
    Added a final test section detailing the robot's functionalities, challenges faced, and potential improvements. Updated the conclusion to reflect the project's outcomes and learnings.
2026-01-16 Remove 'Apprentissages' section from README
    Removed the 'Apprentissages' section from the README.
2026-01-16 Simplify conclusion section in README
    Removed redundant heading for conclusion section.
2026-01-16 Add 'Test final' section to README
2026-01-16 add test motor
    Corrected formatting and added an image for motor test.
2026-01-16 Update test section for motor control and adjustments
    Clarified the PWM control validation and adjustments for motor speeds.
2026-01-16 update authors in README
2026-01-16 Improve image formatting in README
    Updated image formatting in README for better alignment and presentation.
